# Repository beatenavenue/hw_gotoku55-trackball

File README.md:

English | [日本語](README_ja.md)

> They say the trackball journey ends once you buy a Kensington SlimBlade Pro and an Elecom COMFY wrist rest.  
> But couldn't the case be made smaller?

# GOTOKU-55 Trackball

## What is this?
This is a **"part"** for a 55 mm trackball. To see where it fits, you need some background, in order.

### Ploopy Adept
The Adept is a trackball with a 44 mm ball (1.75 in ≈ 44.5 mm), developed by Ploopy, a small Canadian company. The design files and firmware are open source, but parts you source yourself may not fit dimensionally, so buying a kit or a fully assembled unit from the official Ploopy store is recommended.

- Link: [Adept Trackball](https://ploopy.co/adept-trackball/)

### Adept Anyball
Adept Anyball is a mod project that reworks the Adept case so that the ball rides on BTUs (ball transfer units). By choosing a case variant, you can use anything from a small 34 mm ball up to a 68 mm billiard ball. The files are published on GitHub, and you 3D print and assemble them yourself.

There is of course a 55 mm version, but its case is rather large, and many people seem to add a wrist rest to it.

- Link: [Adept Anyball](https://github.com/adept-anyball/)

#### Note: how trackballs support the ball
Most trackballs on the market today hold the ball on static supports, such as ceramic balls. Static supports are quiet, cheap and small, so they will likely stay the mainstream. On the other hand, they always have some friction, and many users have tried things like coating the ball to make it feel better.

Ball bearing supports had fallen out of use, but recently their comfort has been rediscovered, and they seem to be making a comeback. Elecom, for example, now has models with ball bearing supports in its IST and HUGE lines. Friction is low, so when you want to nudge the cursor just a little, precisely, they feel far better than static supports. This is not a special move. It happens all the time at a desk, so it makes a big difference.

Ploopy mainly uses ball bearing supports, but supporting the ball on special parts called BTUs (ball transfer units) has recently become popular. The Anyball project seems to be leading this BTU trend. A BTU is a large ball resting on a bed of tiny balls that let it roll smoothly. In industry, BTUs are used in conveyor tables for moving heavy loads, or as casters.  
A ball bearing turns only about its own axle, while a BTU lets the ball roll freely in any direction. That is why BTUs are sometimes called the ideal way to support a trackball ball.

### ploopy-adept-small-btu v4 (Slim)
A compact case for 34 mm / 38 mm balls by Fabricio Bastian, published within the Anyball project. It is made as low-profile as possible so that it can sit between the halves of a split keyboard, and its design is beautiful and refined.  
Going by the height of the buttons alone, it is probably lower than the Keychron Nape Pro, one of the smallest trackballs on the market. If you like low-profile keyboards, it is very appealing.

- Link: [adept-anyball/ploopy-adept-small-btu](https://github.com/adept-anyball/ploopy-adept-small-btu)

### GOTOKU-55
Putting a 55 mm ball on ploopy-adept-small-btu v4 is quite a stretch. On paper, the ball and the arm that holds it are so big that they almost cover the buttons. But this unpromising idea turned out to work surprisingly well once I built it.  
The lopsided look may surprise you, but it is not as huge as it looks. A 55 mm ball is certainly big for a trackball, but it is much smaller than a baseball.  
Also, there is something I had felt since I first saw the small-btu case. Unlike a typical trackball, the ball is exposed down to its "southern hemisphere". You can wrap your thumb around it as if gripping it, which makes even precise movements steady and comfortable.

So I made an arm part (the "trackball support" in small-btu terms) that holds a 55 mm ball and fits this beautiful compact case. That is GOTOKU-55. The name comes from *gotoku* (五徳), the pronged trivet that holds a pot over a Japanese gas burner, which is what the arm part looks like. The 55 is the ball diameter in millimetres.

In most cases the arm part is all you need. The small-btu v4 case is polished and beautiful, so you can use it as is.

### The arm
There are three versions of the arm.

- **Ball bearing, one-piece version.** For printing in PLA.
- **Ball bearing, split version.** For metal printing. The arm is metal, and the center floor (the cover over the sensor lens) is a separate PLA part.
- **BTU, split version.** It works, but the shape is rather extreme. It uses the same sensor cover as the ball bearing split version.

A 55 mm ball is heavy, and you roll it with your palm. A PLA arm bends outward under this load. So I recommend printing the arm in metal with SLM (metal 3D printing, for example in stainless steel 316L). With a metal arm, the arm does not bend at all. A metal arm alone is enough to fix this problem.  
(If you think a better shape could solve this, I would be glad to hear from you.)

Use a split version for metal printing (the BTU arm comes only as a split version). The PLA floor goes in from below. It is held between the metal arm and the sensor lens, so the heavy metal arm does not press on the lens.

Ball bearings are cheap and comfortable. In most cases, I recommend ball bearings.  
BTUs are popular in the DIY trackball world, but they are expensive. A ball bearing rolls only in the direction at right angles to its axle. So when you roll the ball, some of the bearings slip a little, and when you twist the ball in place, all of them slip. A BTU rolls in any direction without slipping, and the difference is largest when you twist the ball. However, the Adept reads the ball with an optical sensor underneath, and that sensor cannot read the twist, so this brings no real functional benefit. And BTUs are very noisy.  
BTU mods are trendy, and hard to resist. Try it only if you are in it for the romance.

### The case
With a grip like mine, the stock v4 gets in the way. When I lay my thumb flat to press the front buttons, the corner of the case hits my finger.

So, for people who hold it this way, I also made a modified case that extends the front buttons all the way to the edge.
The screw holes and so on are unchanged from v4, so printing only the top is enough. But the front wall disappears and it looks a little bare, so I made a bottom as well.  
This extended-button case is compatible with v4, so you can use the case alone even with a small-btu arm, for example for a 34 mm ball.

Of the back buttons, only the one on your dominant-hand side is really usable. On a symmetrical trackball with a big ball, some buttons are bound to be awkward. But with a 55 mm ball, pressing a back button often means touching the ball too, which gets annoying. It costs the flat look of the beautiful v4 case, which is a hard trade-off, but I also made parts that raise the four back buttons.

## Compatibility
small-btu v4 only.

The arm fits both the original small-btu v4 case and the GOTOKU case.

v5 has a similar shape, so it might work, but by my estimate the ball would probably interfere slightly.

## How to build
See the [build guide](docs/BUILD.md).

## License
Copyright (C) 2026 Kotaro WAJIKI  
Based on ploopy-adept-small-btu v4, Copyright (C) Fabricio Bastian  
Licensed under the GNU General Public License v3.0

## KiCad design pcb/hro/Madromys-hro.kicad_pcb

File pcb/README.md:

English | [日本語](README_ja.md)

# GOTOKU PCB v1

This is a modified version of the Ploopy Madromys PCB (R1.001), the main board of the Ploopy Adept trackball.
The goal is to order the board with assembly (PCBA) from JLCPCB, so that no hand soldering is needed for the small parts.

**This is NOT an official Ploopy product. Do not ask Ploopy for support.**

This board is not built and not tested yet.

## Problem in older data (fixed on 2026-11-18)

In the data before 2026-11-18, the opening for the optical sensor was only 8.6 x 8.6 mm. The lens does not fit into it.
The cause was a mistake in the conversion. Only the square hole of the sensor footprint was made into a cutout, and the outline on the "Board Outline" layer was missed.

If you have boards made from the older data, enlarge the opening to 8.6 x 17.7 mm by hand.
Keep the width, and extend the opening by 4.55 mm at both ends (toward the USB connector and away from it).
The extra area has no copper on any layer. On the board it is the darker green area above and below the opening.
One board was enlarged in this way, and the optical sensor and the buttons worked.

## This board alone is not a complete trackball

JLCPCB assembles all parts in the BOM except the optical sensor. You need to get these parts yourself and solder the sensor by hand.

- The optical sensor PMW3360DM-T2QU and the lens LM19-LSI

## Variants

There are two variants. They differ only in the USB-C connector.

| Folder | USB-C connector | Notes |
|---|---|---|
| [original](original/) | JAE DX07S016JA1R1500 (LCSC C3197885) | Same connector and routing as the original board. |
| [hro](hro/) | HRO TYPE-C-31-M-12 (LCSC C165948) | Slightly cheaper at JLCPCB. Routing around the connector was changed by hand. |

Each folder has these files:

- `*.kicad_pcb` is the board data for KiCad.
- `*-gerber.zip` is the Gerber and drill data.
- `*-BOM-JLC.csv` and `*-CPL-JLC.csv` are the BOM and the placement file for JLCPCB assembly.
- `*-gerber-preview.png` is a preview image of the Gerber data.

## Ordering at JLCPCB

- 4 layers, 0.8 mm thickness
- Assemble top side
- Upload the BOM and the CPL file of the same variant.

The optical sensor (PMW3360DM-T2QU) has no LCSC number in the BOM, so JLCPCB does not assemble it.

The package of the switch D2LS-21 (LCSC C3823622) is not listed on the JLCPCB part page. Check the position and the direction of the switches in the placement preview before you order.

## Changes from the original

The original data is the Altium project in [ploopyco/adept-trackball](https://github.com/ploopyco/adept-trackball) (`hardware/electronics/PCBs/Madromys`, commit `2ec4576`).
Only the PCB was converted. The schematic was not converted. See the original schematic PDF for the circuit.

### Conversion from Altium to KiCad

The board was converted with the Altium importer of KiCad 7.
These fixes were needed after the conversion.

- The opening for the optical sensor is a cutout of 8.6 x 17.7 mm. In the Altium data, this shape is the outline of the sensor footprint on the "Board Outline" layer. The lens goes through this opening.
- The two locating holes of the USB-C connector are now non-plated holes. In the Altium data they are marked as plated, but they have no copper and no net.
- 10 very short broken arcs in the copper were replaced with straight segments.
- The board thickness is set to 0.8 mm. This value comes from the Altium layer stack.

### Parts that are not mounted

These parts are marked as "DNP" (do not populate). They are removed from the BOM and the CPL file. Their pads stay on the board.

| Designator | Part | Reason |
|---|---|---|
| LED.D.1, LED.D.3 | Addressable RGB LED | See "Why the LEDs were removed" below. |
| LED.C.20, LED.C.23, LED.R.9, LED.R.16 | Capacitors and resistors for the LEDs | Not needed without the LEDs. |
| USB.R.12, USB.R.14 | 10k resistor on CC1 and CC2 | The original uses two 10k resistors in parallel on each CC line. This board uses one 5.1k resistor instead. |
| MCU.J.1 | 2-pin header | No header is mounted, same as the original product. The two holes are used to start the bootloader. See below. |

### Why the LEDs were removed

- The official firmware does not enable the LED feature (rgblight). The configuration file still has settings for 3 LEDs and for animations, so an illumination feature may have been planned. The board has only 2 LEDs.
- The LEDs run on 5 V (V_USB), but the data signal comes from the RP2040 at 3.3 V. This leaves only a small margin to the voltage that this type of LED needs to read a high level, so the LEDs may not work as expected.
- The removed parts are all cheap, so removing them does not reduce the cost much.

### Changed values and substitute parts

| Designator | Original | This board |
|---|---|---|
| USB.R.13, USB.R.15 | 10k 1% | 5.1k 1% (one resistor for each CC line) |
| USB.Z.1 | IP4220CZ6 (ESD protection) | SRV05-4 (LCSC C384887). Same pinout. |
| REG.U.4 | AP2204K-1.8 | AP2112K-1.8 (LCSC C176944). Same pinout. |
| MCU.Y.1 | RH100-12.000-16-3030 (12 MHz, 16 pF) | X322512MSB4SI (12 MHz, 20 pF, LCSC C9002). The load capacitors stay at 18 pF. |

REG.C.15 (100 pF) is marked as "not fitted" in the BoM variant of the original project.
On this board it is mounted.

Other passive parts were replaced with common LCSC parts of the same value and size.

### Silkscreen

- The board name "Madromys R1.001 / August 2023" was changed to "GOTOKU PCB v1".
- The label "MCH.FID.1" was hidden.
- A logo and a notice of the modification were added on the top side.

### Holes for an extra button (GP12)

Two plated holes were added above LED.D.1, the LED on the upper right of the optical sensor.
They are marked "GP12" and "GND" on the silkscreen. The pitch is 2.54 mm.

- GP12 (square pad) is connected to GPIO12 of the RP2040. This was the data line for the LEDs (LEDData). It is free because the LEDs are not mounted.
- GND (round pad) is connected to the ground planes.

Connect a switch between the two holes.

**This button does not work with the official Ploopy QMK firmware, even without the LEDs.**
The official firmware does not read GP12.
To use the button, build your own firmware. Add GP12 to the direct pins of the matrix, and add a key for it to the layout and the keymap.

Do not use this button if you mount the LEDs. They use the same pin.

### HRO variant only

The HRO connector has a different pad layout. These changes were made only in the `hro` variant.

- The connector footprint was replaced with `USB_C_Receptacle_HRO_TYPE-C-31-M-12` from the KiCad library. The position and the direction are the same as the original connector.
- The D+, D-, CC1, CC2 and VBUS traces near the connector were changed to fit the new pads.
- One VBUS via was moved, and one GND via under the connector was removed.
- The copper pour was cleared around the new traces and pads.

The connections and the clearances near the connector were checked with a script.
**A full DRC has not been run yet. Run the DRC in KiCad 8 or later before you order this variant.**
`Madromys-usb-area-orig-vs-hro.png` shows the area around the connector in both variants.

## How the fabrication data is checked

The scripts in [tools](tools/) check the Gerber and drill files against the original Altium file.
They read the Altium file directly and do not use KiCad, so mistakes in the conversion can be found.

- `verify_fab.py` compares the board outline, the cutouts and all drill holes.
  The "Board Outline" layer of the Altium file, including the outlines inside footprints, is used as the board outline.
- `edge_clearance.py` reports the distance from copper on all layers to the sensor cutout.
- `export.sh` exports the Gerber and drill files with the settings used for the zip files.

Expected differences reported by `verify_fab.py`:

- The 8.6 mm square hole of the sensor footprint (U2) is not drilled. It is inside the sensor cutout.
- The two locating holes of the USB-C connector (J3) are non-plated. See "Conversion from Altium to KiCad".
- The two holes for the extra button (GP12 and GND) are added.
- HRO variant only. The holes of the USB-C connector and two vias next to it are different.

Usage:

```
python3 tools/verify_fab.py <adept-trackball>/hardware/electronics/PCBs/Madromys/Madromys.PcbDoc <folder with the unzipped Gerber files>
```

## Starting the bootloader

You do not need this for the first firmware upload.
A new board has an empty flash memory, so the RP2040 starts in the bootloader (BOOTSEL mode) automatically.

To update the firmware later, hold the bottom left button (matrix [0,0]) while you plug in the USB cable.

If the firmware is broken and the button does not work, use the two holes of MCU.J.1 near LED.D.3.
Connect the two holes with metal tweezers, and plug in the USB cable at the same time.
One hole is GND. The other hole is connected to the chip select line of the flash memory through a 1k resistor.

## License

The files in this folder are licensed under the CERN Open Hardware Licence Version 2, Strongly Reciprocal (CERN-OHL-S-2.0).
See [LICENSE](LICENSE).
This is different from the rest of this repository, which uses GPL-3.0.

- Original design: Ploopy Madromys R1.001 (Ploopy Adept) by Ploopy Corporation, licensed under CERN-OHL-S-2.0.
  Source: https://github.com/ploopyco/adept-trackball
- Modifications: Copyright (C) 2026 Kotaro WAJIKI. Modified on 2026-10-11. The changes are listed in "Changes from the original" above.
- Source Location of this modified design: https://github.com/beatenavenue/hw_gotoku55-trackball/tree/main/pcb

This design is provided "as is", without any warranty. See section 6 of the license.

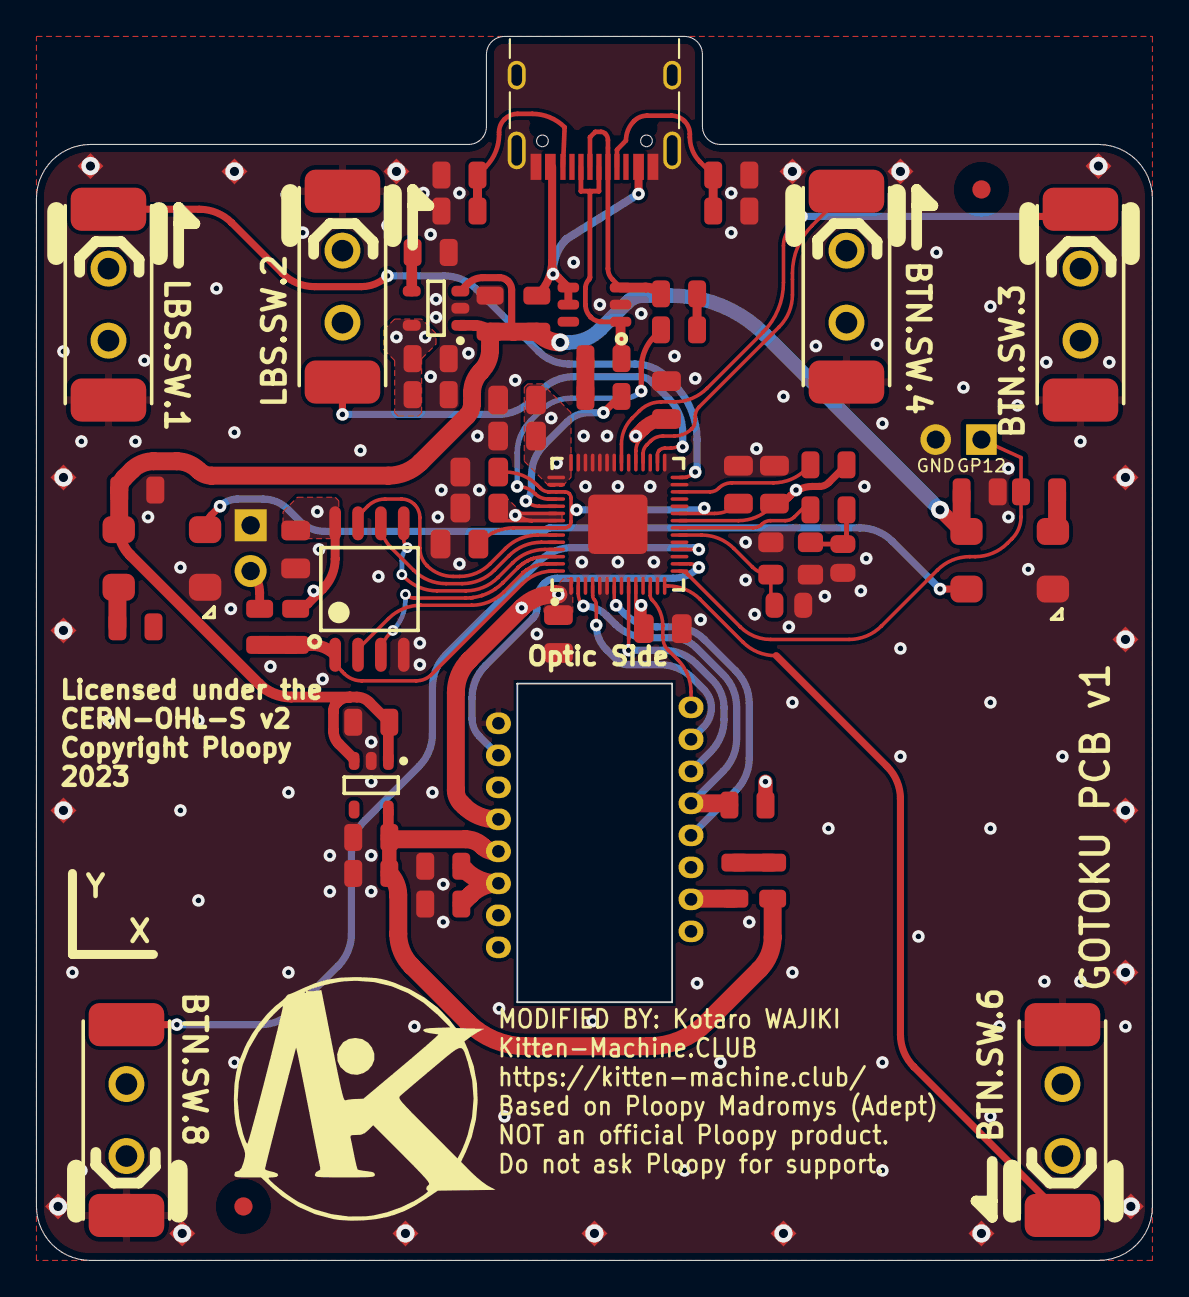
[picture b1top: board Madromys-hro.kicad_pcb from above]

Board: 4 copper layers, 62.0 x 68.0 mm, 84 parts (1 on the bottom side), 45 nets.

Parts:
BTN.J.9: EXT BUTTON; EXT_BUTTON_2x1
BTN.SW.3, BTN.SW.4, BTN.SW.6, BTN.SW.8: D2LS-21
KM.LOGO.1: KM_LOGO
LBS.SW.1, LBS.SW.2: D2LS-21
LED.C.20, LED.C.23, LED.R.9, LED.R.16: DNP 0805; 0805
LED.D.1, LED.D.3: DNP IN-PI55TATPRPGPB; IN-PI55TATPRPGPB
MCH.FID.1, MCH.FID.2: IPC-7351 Fiducial 1mm; FIDUCIAL_1.5
MCH.LOGO.2: Coordinate system marker for assembly; Coordinate System
MCH.SP.1, MCH.SP.2, MCH.SP.3, MCH.SP.4, MCH.SP.5, MCH.SP.6, MCH.SP.7, MCH.SP.8, MCH.SP.9, MCH.SP.10, MCH.SP.11, MCH.SP.12, MCH.SP.13, MCH.SP.14, MCH.SP.15, MCH.SP.16, MCH.SP.17, MCH.SP.18, MCH.SP.19, MCH.SP.20: Spark Gap; SparkGap
MCU.C.1, MCU.C.2, MCU.C.3, MCU.C.4, MCU.C.5, MCU.C.6, MCU.C.7, MCU.C.8, MCU.C.21, MCU.C.22, MCU.C.24: 0805 X5R; 0805 - TALL
MCU.C.9, MCU.C.19: 0603
MCU.J.1: DNP HEADER2; 2x1
MCU.R.1, MCU.R.2, MCU.R.11, MCU.R.17: 0805
MCU.U.1: W25Q16JVSSIQ; W25Q128JVS - SOIC127P790X216-8M
MCU.U.5: RP2040; RP2040 - QFN40P700X700X90_HS-57M
MCU.Y.1: RH100-12.000-16-3030
MOS.C.10, MOS.C.11, MOS.R.3, MOS.R.4, MOS.R.5: 0805
MOS.U.2: PMW3360DM-T2QU
REG.C.12, REG.C.13, REG.C.14, REG.C.15, REG.C.16, REG.C.17, REG.C.18: 0805
REG.U.3: AP2202K-3.3; AP2202 - SOT95P270X145-5N
REG.U.4: AP2204K-1.8; AP2202 - SOT95P270X145-5N
USB.FB.1, USB.FB.2, USB.FB.3: ACML-0805-601-T; 0805
USB.J.3: TYPE-C-31-M-12; USB_C_Receptacle_HRO_TYPE-C-31-M-12
USB.R.6, USB.R.7: 0805
USB.R.12, USB.R.14: DNP 0805; 0805
USB.R.13, USB.R.15: 5.1k 1%; 0805
USB.Z.1: IP4220CZ6,125; PESD3V3S4UD - SOT95P275X110-6N

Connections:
1V1: MCU.C.21.2, MCU.C.22.2, MCU.C.24.2, MCU.U.5.23, MCU.U.5.45, MCU.U.5.50
1V8: MOS.R.3.2, MOS.U.2.4, REG.C.17.2, REG.C.18.2, REG.U.4.5
3V3: MCU.C.1.2, MCU.C.2.2, MCU.C.3.2, MCU.C.4.2, MCU.C.5.2, MCU.C.6.2, MCU.C.7.2, MCU.C.8.2, MCU.R.2.1, MCU.R.17.1, MCU.U.1.8, MCU.U.5.1, MCU.U.5.10, MCU.U.5.22, MCU.U.5.33, MCU.U.5.42, MCU.U.5.43, MCU.U.5.44, MCU.U.5.48, MCU.U.5.49, MOS.R.5.2, MOS.U.2.5, REG.C.13.2, REG.C.14.2, REG.U.3.5
GND: BTN.J.9.2, BTN.SW.3.B, BTN.SW.4.B, BTN.SW.6.B, BTN.SW.8.A, LBS.SW.1.B, LBS.SW.2.A, LED.C.20.1, LED.C.23.1, LED.D.1.3, LED.D.3.3, MCH.SP.1.1, MCH.SP.2.1, MCH.SP.3.1, MCH.SP.4.1, MCH.SP.5.1, MCH.SP.6.1, MCH.SP.7.1, MCH.SP.8.1, MCH.SP.9.1, MCH.SP.10.1, MCH.SP.11.1, MCH.SP.12.1, MCH.SP.13.1, MCH.SP.14.1, MCH.SP.15.1, MCH.SP.16.1, MCH.SP.17.1, MCH.SP.18.1, MCH.SP.19.1, MCH.SP.20.1, MCU.C.1.1, MCU.C.2.1, MCU.C.3.1, MCU.C.4.1, MCU.C.5.1, MCU.C.6.1, MCU.C.7.1, MCU.C.8.1, MCU.C.9.2, MCU.C.19.1, MCU.C.21.1, MCU.C.22.1, MCU.C.24.1, MCU.J.1.1, MCU.U.1.4, MCU.U.5.3, MCU.U.5.5, MCU.U.5.6, MCU.U.5.8, MCU.U.5.11, MCU.U.5.13, MCU.U.5.17, MCU.U.5.19, MCU.U.5.27, MCU.U.5.29, MCU.U.5.31, MCU.U.5.34, MCU.U.5.36, MCU.U.5.37, MCU.U.5.38, MCU.U.5.39, MCU.U.5.40, MCU.U.5.41, MCU.U.5.57, MCU.Y.1.2, MCU.Y.1.4, MOS.C.10.1, MOS.C.11.1, MOS.U.2.8, REG.C.12.1, REG.C.13.1, REG.C.14.1, REG.C.15.1, REG.C.16.1, REG.C.17.1, REG.C.18.1, REG.U.3.2, REG.U.4.2, USB.J.3.A1, USB.J.3.A12, USB.J.3.B1, USB.J.3.B12, USB.J.3.S1, USB.R.12.1, USB.R.13.1, USB.R.14.1, USB.R.15.1, USB.Z.1.2
LEDData: BTN.J.9.1, LED.R.16.2, MCU.U.5.15
NetBTN.SW.3_A: BTN.SW.3.A, MCU.U.5.35
NetBTN.SW.4_A: BTN.SW.4.A, MCU.U.5.32
NetBTN.SW.6_A: BTN.SW.6.A, MCU.U.5.14
NetBTN.SW.8_B: BTN.SW.8.B, MCU.U.5.18
NetLBS.SW.1_A: LBS.SW.1.A, MCU.U.5.28
NetLBS.SW.2_B: LBS.SW.2.B, MCU.U.5.30
NetLED.D.1_2: LED.D.1.2, LED.D.3.4
NetLED.D.1_4: LED.D.1.4, LED.R.16.1
NetLED.D.3_2: LED.D.3.2, LED.R.9.2
NetMCU.C.9_1: MCU.C.9.1, MCU.U.5.20, MCU.Y.1.1
NetMCU.C.19_2: MCU.C.19.2, MCU.R.11.2, MCU.Y.1.3
NetMCU.J.1_2: MCU.J.1.2, MCU.R.1.1
NetMCU.R.1_2: MCU.R.1.2, MCU.R.2.2, MCU.U.1.1, MCU.U.5.56
NetMCU.R.11_1: MCU.R.11.1, MCU.U.5.21
NetMCU.R.17_2: MCU.R.17.2, MCU.U.5.26
NetMCU.U.1_2: MCU.U.1.2, MCU.U.5.55
NetMCU.U.1_3: MCU.U.1.3, MCU.U.5.54
NetMCU.U.1_5: MCU.U.1.5, MCU.U.5.53
NetMCU.U.1_6: MCU.U.1.6, MCU.U.5.52
NetMCU.U.1_7: MCU.U.1.7, MCU.U.5.51
NetMCU.U.5_2: MCU.U.5.2, MOS.R.5.1, MOS.U.2.12
NetMCU.U.5_4: MCU.U.5.4, MOS.U.2.10
NetMCU.U.5_7: MCU.U.5.7, MOS.U.2.13
NetMCU.U.5_9: MCU.U.5.9, MOS.U.2.11
NetMCU.U.5_12: MCU.U.5.12, MOS.U.2.9
NetMCU.U.5_16: MCU.U.5.16, MOS.U.2.7
NetMCU.U.5_46: MCU.U.5.46, USB.R.6.2
NetMCU.U.5_47: MCU.U.5.47, USB.R.7.2
NetMOS.C.10_2: MOS.C.10.2, MOS.C.11.2, MOS.U.2.3
NetMOS.R.3_1: MOS.R.3.1, MOS.R.4.2
NetMOS.R.4_1: MOS.R.4.1, MOS.U.2.15
NetREG.C.15_2: REG.C.15.2, REG.U.3.4
NetUSB.FB.1_1: USB.FB.1.1, USB.J.3.A4, USB.J.3.A9, USB.J.3.B4, USB.J.3.B9, USB.Z.1.4, USB.Z.1.5
NetUSB.FB.2_1: USB.FB.2.1, USB.J.3.A7, USB.J.3.B7, USB.Z.1.3
NetUSB.FB.2_2: USB.FB.2.2, USB.R.6.1
NetUSB.FB.3_1: USB.FB.3.1, USB.J.3.A6, USB.J.3.B6, USB.Z.1.1
NetUSB.FB.3_2: USB.FB.3.2, USB.R.7.1
NetUSB.J.3_3: USB.J.3.A5, USB.R.14.2, USB.R.15.2
NetUSB.J.3_9: USB.J.3.B5, USB.R.12.2, USB.R.13.2
V_USB: LED.C.20.2, LED.C.23.2, LED.D.1.1, LED.D.3.1, REG.C.12.2, REG.C.16.2, REG.U.3.1, REG.U.3.3, REG.U.4.1, REG.U.4.3, USB.FB.1.2

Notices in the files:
pcb/hro/Madromys-hro.kicad_pcb:
CERN-OHL-S v2
Copyright Ploopy
